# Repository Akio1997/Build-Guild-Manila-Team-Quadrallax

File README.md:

# Build Guild Manila = Team Quadrallax
## Meet "LEGS"!
Legs is a macropad designed to help you set shortcuts for different programs/softwares - whether it be games or tools.

**Legs is comprised of:**
- 4 Switches, 3 are assigned to keyboard shortcuts for different applications that the user sets. The other is assigned to switching between said keyboard shortcuts (for example, you can switch between having keyboard shortcuts for Davinci Resolve and OSU!.)
- 3 LEDs helping you see which mode/keyboard shortcuts are activated
- A Cover that serves as the macropad's protection when closed, and serves as a small notepad holder when opened.

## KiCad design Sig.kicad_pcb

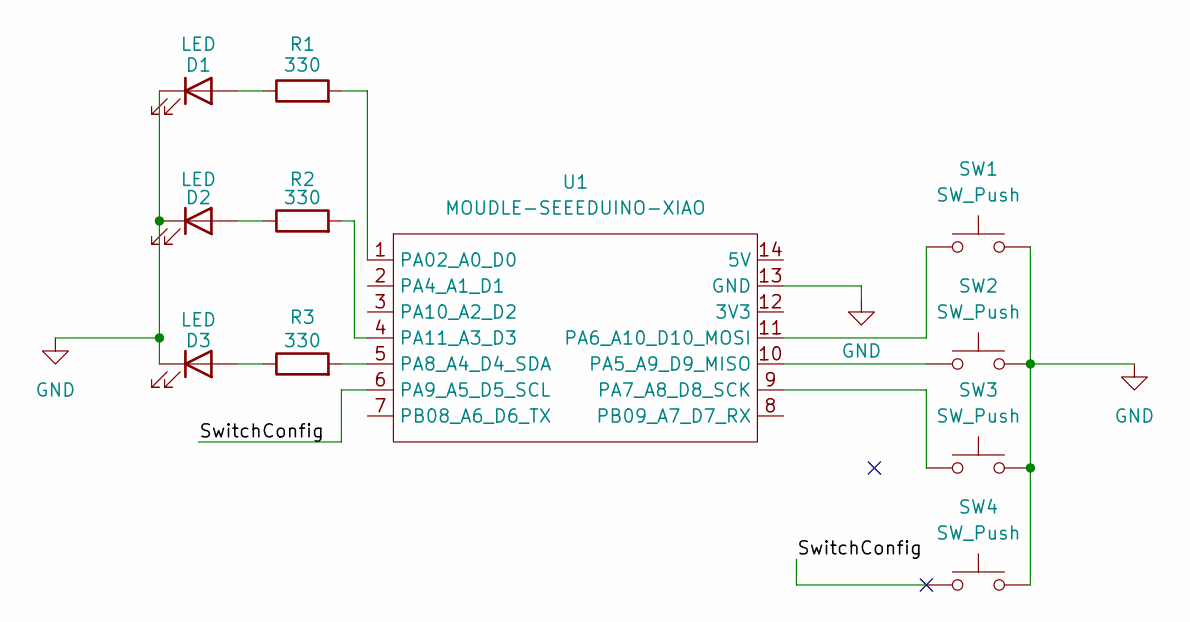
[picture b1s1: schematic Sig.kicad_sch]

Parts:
D1, D2, D3: LED; LED_D5.0mm_IRBlack
R1, R2, R3: 330; R_Axial_DIN0204_L3.6mm_D1.6mm_P7.62mm_Horizontal
SW1, SW2, SW3, SW4: SW_Push; SW_Cherry_MX_1.00u_PCB
U1: MOUDLE-SEEEDUINO-XIAO; XIAO-Generic-Hybrid-14P-2.54-21X17.8MM

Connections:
/SwitchConfig: SW4.1, U1.6 (PA9_A5_D5_SCL)
GND: D1.1 (K), D2.1 (K), D3.1 (K), SW1.2, SW2.2, SW3.2, SW4.2, U1.13 (GND)
unnamed: D1.2 (A), R1.1
unnamed: D2.2 (A), R2.1
unnamed: D3.2 (A), R3.1
unnamed: R1.2, U1.1 (PA02_A0_D0)
unnamed: SW2.1, U1.10 (PA5_A9_D9_MISO)
unnamed: SW1.1, U1.11 (PA6_A10_D10_MOSI)
unnamed: SW3.1, U1.9 (PA7_A8_D8_SCK)
unnamed: R3.2, U1.5 (PA8_A4_D4_SDA)
unnamed: R2.2, U1.4 (PA11_A3_D3)

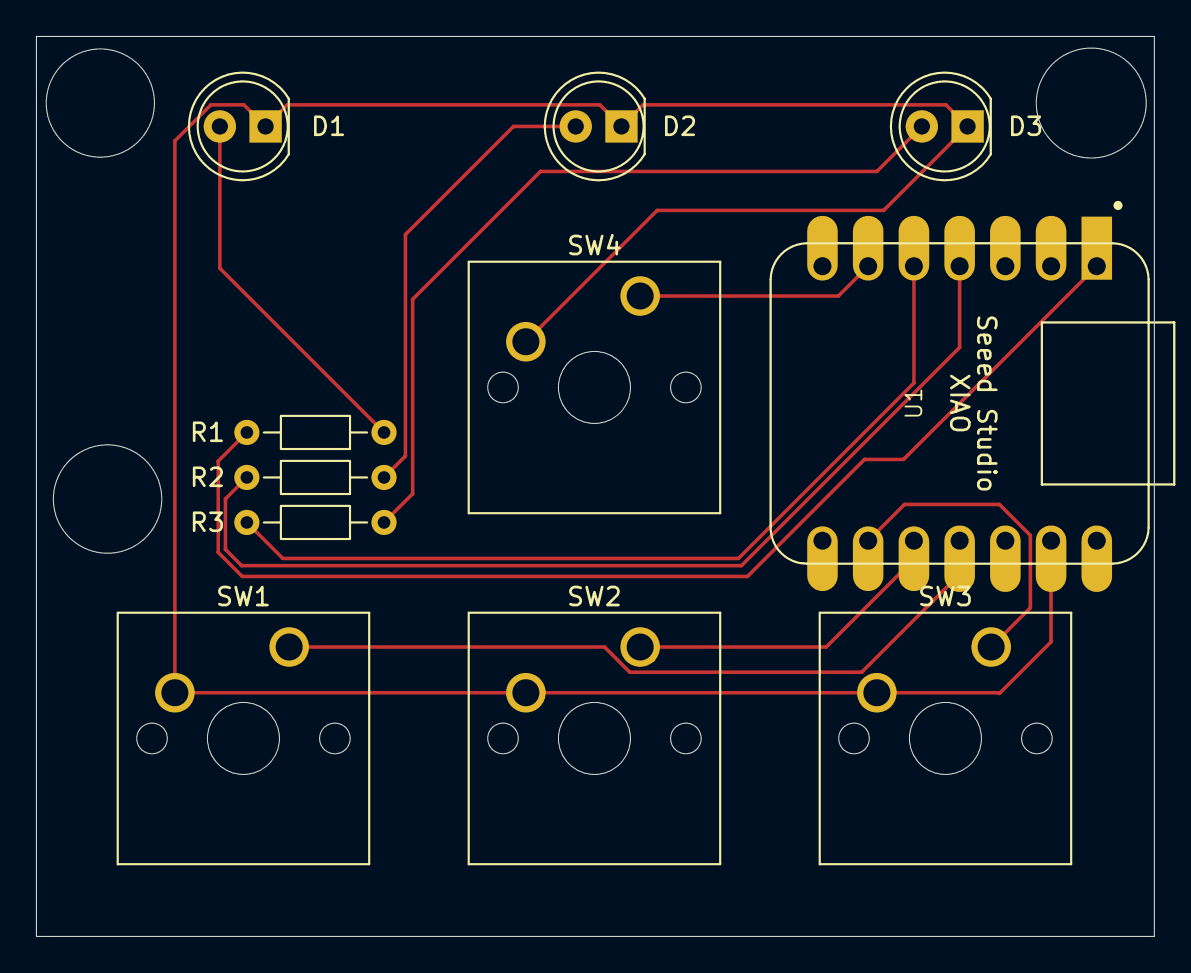
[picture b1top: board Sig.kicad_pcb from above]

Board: 2 copper layers, 62.1 x 50.0 mm, 11 parts (0 on the bottom side), 11 nets.

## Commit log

2026-05-02 Initial commmit
2026-05-02 feat: add KiCad files
2026-05-02 feat: delete kicad_mod file
2026-05-02 feat: add 3d picture and sketches
